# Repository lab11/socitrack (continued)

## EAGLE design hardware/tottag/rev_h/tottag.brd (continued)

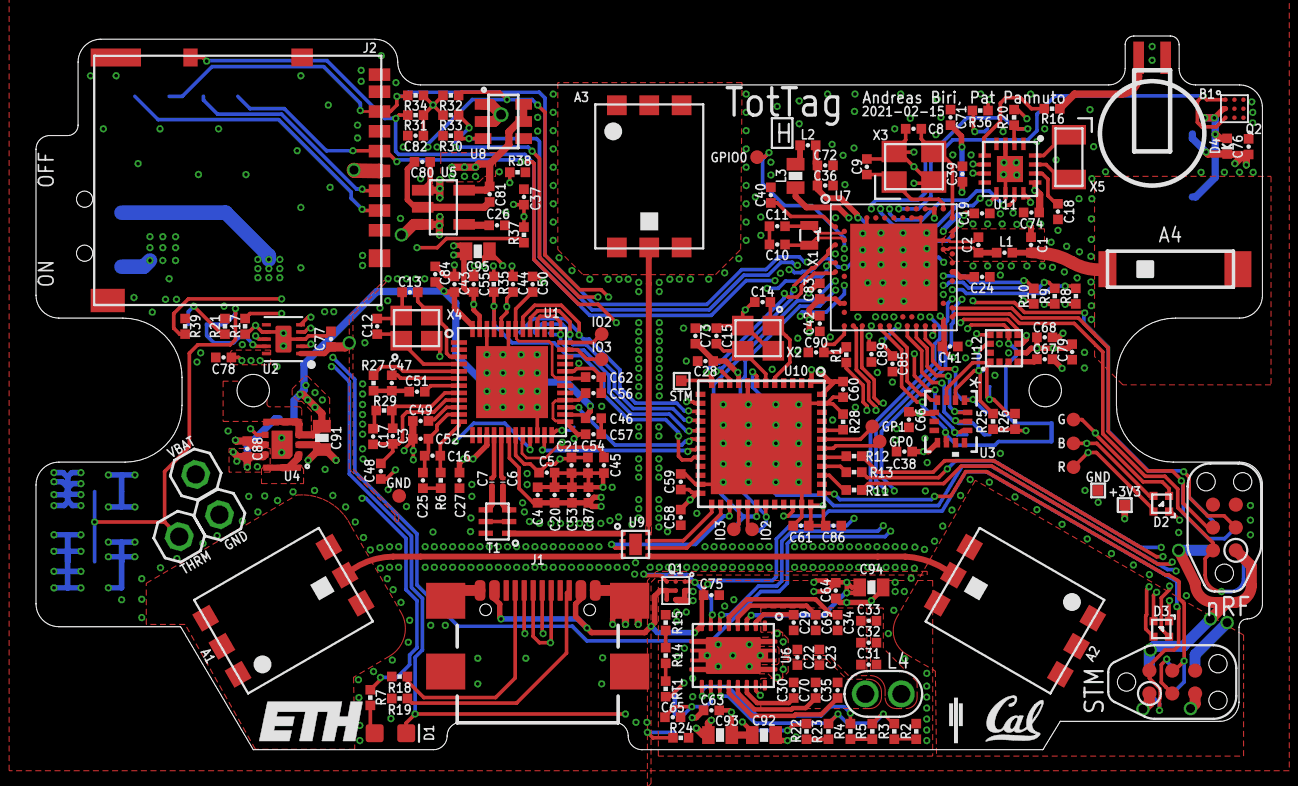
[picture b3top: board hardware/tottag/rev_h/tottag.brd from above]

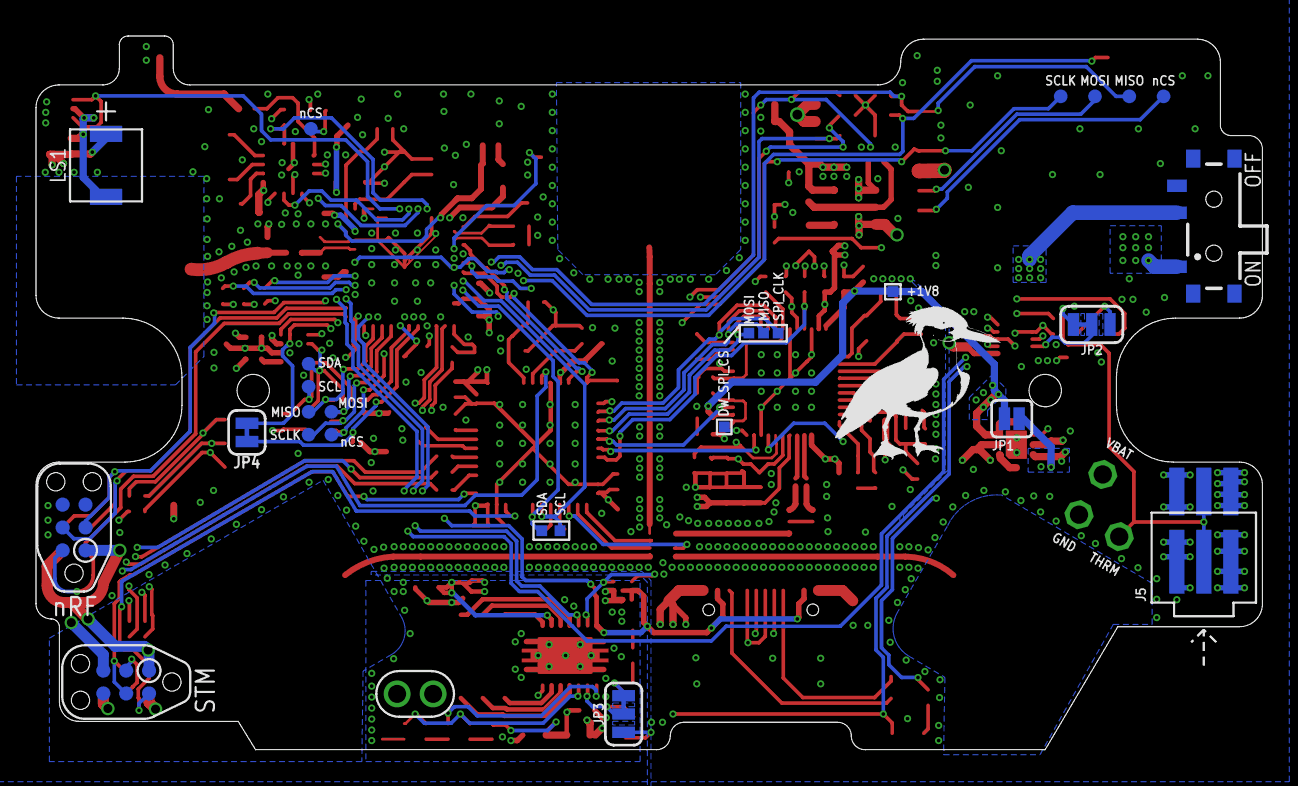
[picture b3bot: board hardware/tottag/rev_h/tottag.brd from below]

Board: 4 copper layers, 68.1 x 39.6 mm, 218 parts (26 on the bottom side), 150 nets.

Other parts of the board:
U$1: TOTTERNARY_300MIL
U$2: UCSD_TRIDENT_SOLID_100MIL
U$3: ETH_200MIL
U$4: UCB_CAL_100MIL

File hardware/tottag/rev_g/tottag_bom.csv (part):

# Bill of Materials,,,,,,,,,,,,
# Converted from {},,,,,,,,,,,,
# Generated by bom_to_text.py,,,,,,,,,,,,
#,,,,,,,,,,,,
,,,,,,,,,,,,
Qty,Parts,Value,Can Substitue,Do Not Populate (DNP),Device,Package,Description,DESCRIPTION,DIGIKEY,MANUFACTURER,MPN,MOUSER
3,"A1, A2, A3",TAIYO-YUDEN-AH086M,N,,TAIYO-YUDEN-AH086M,TAIYO-YUDEN-AH086M,UWB Antenna - 3.1-8GHz,,587-2204-1-ND,,AH086M555003-T,
1,A4,AMCA72-2R47G-S1F-T,N,,AMCA72-2R47G-S1F-T,AMCA72-2R470G-S1F-T,"WiFi/Bluetooth/ZigBee, ISM Atenna",RF ANT 2.4GHZ CHIP SOLDER SMD,535-14108-1-ND,,AMCA72-2R470G-S1F-T4,
1,C1,0.5pF,ASK,,CAPACITOR0402_CAP,0402_CAP,SMD Capacitor,,490-11250-1-ND,,GJM1555C1HR50WB01D,
1,C2,0.8pF,ASK,,CAPACITOR0402_CAP,0402_CAP,SMD Capacitor,,490-11253-1-ND,,GJM1555C1HR80WB01D,
1,C3,1.2pF,ASK,,CAPACITOR0402_CAP,0402_CAP,SMD Capacitor,,490-3085-1-ND,,GJM1555C1H1R2CB01D,
2,"C4, C5",10pF,Y,,CAPACITOR0402_CAP,0402_CAP,SMD Capacitor,,732-12054-1-ND,,885012005074,
2,"C6, C7",12pF,ASK,,CAPACITOR0201_CAP,0201_CAP,SMD Capacitor,,399-8604-2-ND,,CBR02C120F3GAC,
8,"C8, C9, C10, C11, C12, C13, C14, C15",12pF,ASK,,CAPACITOR0402_CAP,0402_CAP,SMD Capacitor,,399-8815-2-ND,,CBR04C120F5GAC,
1,C16,18pF,ASK,,CAPACITOR0402_CAP,0402_CAP,SMD Capacitor,,399-8828-1-ND,,CBR04C180F5GAC,
1,C17,27pF,ASK,,CAPACITOR0402_CAP,0402_CAP,SMD Capacitor,,490-16380-1-ND,,GJM1555C1H270FB01D,
1,C18,47pF,Y,,CAPACITOR0402_CAP,0402_CAP,SMD Capacitor,,490-5942-1-ND,,GRM1555C1H470JA01D ,
1,C19,100pF,Y,,CAPACITOR0402_CAP,0402_CAP,SMD Capacitor,,490-5922-1-ND,,GRM1555C1H101JA01D ,
2,"C20, C21",330pF,Y,,CAPACITOR0402_CAP,0402_CAP,SMD Capacitor,,311-3768-1-ND,,CC0402JRX7R9BB331,
2,"C22, C23",470pF,Y,,CAPACITOR0402_CAP,0402_CAP,SMD Capacitor,CAP CER 470PF 50V C0G/NP0 0402,490-6242-1-ND,Murata,GRM1555C1H471JA01J,
2,"C24, C25",820pF,ASK,,CAPACITOR0402_CAP,0402_CAP,SMD Capacitor,,399-11129-2-ND,,C0402C821J5GACTU,
5,"C26, C27, C28, C29, C30",10nF,Y,,CAPACITOR0402_CAP,0402_CAP,SMD Capacitor,,490-6351-2-ND,,GRM155R71H103KA88J,
5,"C31, C32, C33, C34, C35",22nF,ASK,,CAPACITOR0402_CAP,0402_CAP,SMD Capacitor,,311-3823-1-ND,,CC0402ZRY5V8BB223,
1,C36,47nF,Y,,CAPACITOR0402_CAP,0402_CAP,SMD Capacitor,,445-1264-1-ND,,C1005X7R1C473K050BC ,
29,"C37, C38, C39, C40, C41, C42, C43, C44, C45, C46, C47, C48, C49, C50, C51, C52, C53, C54, C55, C56, C57, C58, C59, C60, C61, C62, C63, C64, C65",0.1uF,Y,,CAPACITOR0402_CAP,0402_CAP,SMD Capacitor,,399-C0402C104K4RAC7411TR-ND,,C0402C104K4RAC7411,
2,"C66, C67",470nF,Y,,CAPACITOR0402_CAP,0402_CAP,SMD Capacitor,,490-12270-1-ND,,GRT155R61E474ME01D,
8,"C68, C69, C70, C71, C72, C73, C74, C75",1uF,Y,,CAPACITOR0402_CAP,0402_CAP,SMD Capacitor,,490-7195-1-ND ,,GRM155R70G105KA12D ,
11,"C76, C77, C78, C79, C80, C81, C82, C83, C84, C85, C86",4.7uF,Y,,CAPACITOR0402_CAP,0402_CAP,SMD Capacitor,CAP CER 4.7UF 6.3V X5R 0402,445-13820-2-ND,TDK,C1005X5R1A475K050BC,
5,"C87, C88, C89, C90, C91",10uF,Y,,CAPACITOR0603_CAP,0603_CAP,SMD Capacitor,,1253-CM105X5R106M25ATCT-ND,,CM105X5R106M25AT,
1,C92,47uF,Y,,CAPACITOR0603_CAP,0603_CAP,SMD Capacitor,,490-13247-1-ND,,GRM188R60J476ME15D,
1,D1,GREEN,Y,,LED0603,LED-0603,LED (Generic),,160-1446-1-ND,,LTST-C191KGKT,
2,"D2, D3",SML-LX0404SIUPGUSB,Y,,SML-LX0404SIUPGUSB,1MM_SQ_4PAD,1mm^2 RGB LED,,67-2125-1-ND,Lumex Opto,SML-LX0404SIUPGUSB,
1,D4,DIODE0402,Y,,DIODE0402,0402_DIODE,,,641-2087-1-ND,,CDSQR400B-HF,
1,J1,USB4110-GF-A,N,,USB4110-GF-A,GCT_USB4110-GF-A,CONN USB 2.0 TYPE-C R/A SMT," USB-C (USB TYPE-C) USB 2.0 Receptacle Connector 24 (16+8 Dummy) Position Surface Mount, Right Angle",2073-USB4110-GF-A-1-ND,,USB4110-GF-A,
1,J2,DM3AT-SF-PEJM5,N,,DM3AT-SF-PEJM5,DM3AT-SF-PEJM5,CONN MICRO SD R/A PUSH-PUSH SMD,CONN MICRO SD CARD PUSH-PUSH R/A,HR1964CT-ND,Hirose Electric Co Ltd,DM3AT-SF-PEJM5,
1,J5,MOLEX-PICO-SPOX-3SIDE,N,,MOLEX-PICO-SPOX-3SIDE,MOLEX-PICO-SPOX-3_SIDE,MOLEX,,WM7647CT-ND,,874380343,
1,L1,4.7nH,ASK,,INDUCTOR0402,0402_CAP,A very specific inductor,,490-15482-1-ND,,LQW15AN4N7G8ZD,
1,L2,15nH,ASK,,INDUCTOR0402,0402_CAP,A very specific inductor,,587-1521-1-ND,,HK100515NJ-T ,
1,L3,10uH,ASK,,INDUCTOR0603,0603_CAP,A very specific inductor,,490-4025-1-ND,,LQM18FN100M00D ,
1,LS1,PUI_SMT-0440-T-2-R,N,,PUI_SMT-0440-T-2-R,SMT-0440-T-2-R,,,668-SMT-0440-T-2-RTR-ND,,SMT-0440-T-2-R,
2,"Q1, Q2",CSD75207W15,N,,CSD75207W15,DSBGA,"low on resistance, gate charge dual p-channel nexfet",,296-40008-1-ND,TEXAS INSTRUMENTS,CSD75207W15,
1,R1,4.7,Y,,RESISTOR0402_RES,0402_RES,Resistor,,RMCF0402FT4R70CT-ND,,RMCF0402FT4R70,
2,"R2, R3",97.6,ASK,,RESISTOR0402_RES,0402_RES,Resistor,,RMCF0402FT97R6CT-ND,,RMCF0402FT97R6,
2,"R4, R5",162,ASK,,RESISTOR0402_RES,0402_RES,Resistor,,RMCF0402FT162RCT-ND,,RMCF0402FT162R,
1,R6,270,Y,,RESISTOR0402_RES,0402_RES,Resistor,,RMCF0402FT270RCT-ND,,RMCF0402FT270R,
9,"R7, R8, R9, R10, R11, R12, R13, R14, R15",1k,Y,,RESISTOR0402_RES,0402_RES,Resistor,,RMCF0402FT1K00CT-ND,,RMCF0402FT1K00,
1,R16,1.41k,Y,,RESISTOR0402_RES,0402_RES,Resistor,,RMCF0402FT1K40CT-ND,,RMCF0402FT1K40,
1,R17,2.2k,Y,,RESISTOR0402_RES,0402_RES,Resistor,,RMCF0402JT2K20CT-ND,,RMCF0402JT2K20,
2,"R18, R19",5.1k,Y,,RESISTOR0402_RES,0402_RES,Resistor,,RMCF0402FT5K10CT-ND,,RMCF0402FT5K10,
5,"R20, R21, R22, R23, R24",10k,Y,,RESISTOR0402_RES,0402_RES,Resistor,,RMCF0402FT10K0CT-ND,,RMCF0402FT10K0,
2,"R25, R26",11k,Y,,RESISTOR0402_RES,0402_RES,Resistor,,RMCF0402FT11K0CT-ND,,RMCF0402FT11K0,
1,R27,16k,Y,,RESISTOR0402_RES,0402_RES,Resistor,,RMCF0402FT16K0CT-ND,,RMCF0402FT16K0,
7,"R28, R29, R30, R31, R32, R33, R34",100k,Y,,RESISTOR0402_RES,0402_RES,Resistor,,RMCF0402JT100KCT-ND,,RMCF0402JT100K,
1,R35,3.3M,Y,,RESISTOR0402_RES,0402_RES,Resistor,,RMCF0402FT3M30CT-ND,,RMCF0402FT3M30,
1,R36,10M,Y,,RESISTOR0402_RES,0402_RES,Resistor,,RMCF0402FT10M0CT-ND,,RMCF0402FT10M0,
1,R37,DNP,,DNP,RESISTOR0402_RES,0402_RES,Resistor,,,,,
1,RT1,10k@25C,ASK,,THERMISTOR0402,0402_RES,Thermistor.,,490-18149-1-ND,,NCU15XH103F60RC,
1,S1,,N,,450404015514,450404015514,"WS-SLSU Mini Slide Switch, Same Side Connection Side Push 6.7x2.7 mm",,732-13665-1-ND,,450404015514,
1,T1,HHM1595A1,N,,HHM1595A1,EIA-0805,"Description: Symbol for HHM1595A1, a multilayer Balun from TDK.",XFMR BALUN RF 3.0-8.0GHZ UWB SMD,445-3387-1-ND,TDK Corporation,HHM1595A1,810-HHM1595A1
1,U1,DW1000,N,,DW1000,QFN-48-DW1000,"Description: The DecaWave DW1000 chip, used for UWB two-way ranging.",IC RF TXRX 802.15.4 48-QFN,1479-1001-1-ND,Decawave Limited,DW1000-I-TR13,
1,U2,BQ24040,N,,BQ24040,DSQ0010A,Simple Li Ion / Li Poly charger.,,296-37142-1-ND,,BQ24040,
1,U3,LIS2DW12,N,,LIS2DW12,LGA-12,ultra low power 3 axis accelerometer,,497-17718-6-ND,STMicroelectronics,LIS2DW12TR,511-LIS2DW12TR
1,U4,1.8V,N,,XCL206B,XCL20X,Non-Isolated PoL Module DC DC Converter 1 Output 1.8V 600mA 2V - 6V Input,,893-1406-2-ND,,XCL206B183CR-G,
1,U5,MAX8887EZK33+T,N,,MAX8887EZK33+T,SOT-23-5,IC REG LDO 3.3V 0.3A TSOT23-5,,MAX8887EZK33+TCT-ND,,,
1,U6,BQ51013B,N,,BQ51013B,RHL0020A,bq51013B,,296-38885-1-ND,,BQ51013B,
1,U7,NRF52840,N,,NRF52840,AQFN73,"ultra-low power 2.4 GHz wireless system on chip (SoC) integrating a multiprotocol 2.4 GHz transceiver, an ARM® Cortex®-M4F CPU.",,1490-1071-1-ND,NORIDIC SEMICONDUCTOR,NRF52840,
1,U8,SIP32510,N,,SIP32510,TSOT23-6,"Load switch, slew rate controlled. By Vishay",, SIP32510DT-T1-GE3CT-ND,Vishay,SIP32510DT-T1-GE3,
1,U9,SKY13317,N,,SKY13317,MLPQ-UT-8,"Description: Device for SKY13317-373LF, an RF switch from Skyworks Inc.",IC SWITCH RF SP3T 8-MLP,863-1056-1-ND,Skyworks Solutions Inc.,SKY13317-373LF,
1,U10,STM32F091CC,N,,STM32F091CC,UFQFPN-48,"Description: STM32F091CC from STMicroelectronics, an ARM-based 32-bit MCU with 256 kB Flash, 32kB of SRAM and a Cortex M0",IC MCU 32BIT 256KB FLASH 48QFPN,497-15813-ND,STMicroelectronics,STM32F091CCU6,511-STM32F091CCU6
1,U11,AB1815-T3,N,,AB1815-T3,QFN-16-3MM,Ultra-low current RTC. 55nA quiescent @ 3V. 1.5-3.6V input.,,535-11936-1-ND,Abracon,AB1815-T3,
1,X1,32.768kHz,N,,ABS05-32.768KHZ-9-T,ABS05,32.768kHz Crystal,,535-11897-1-ND,Abracon,ABS05-32.768KHZ-9-T,
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
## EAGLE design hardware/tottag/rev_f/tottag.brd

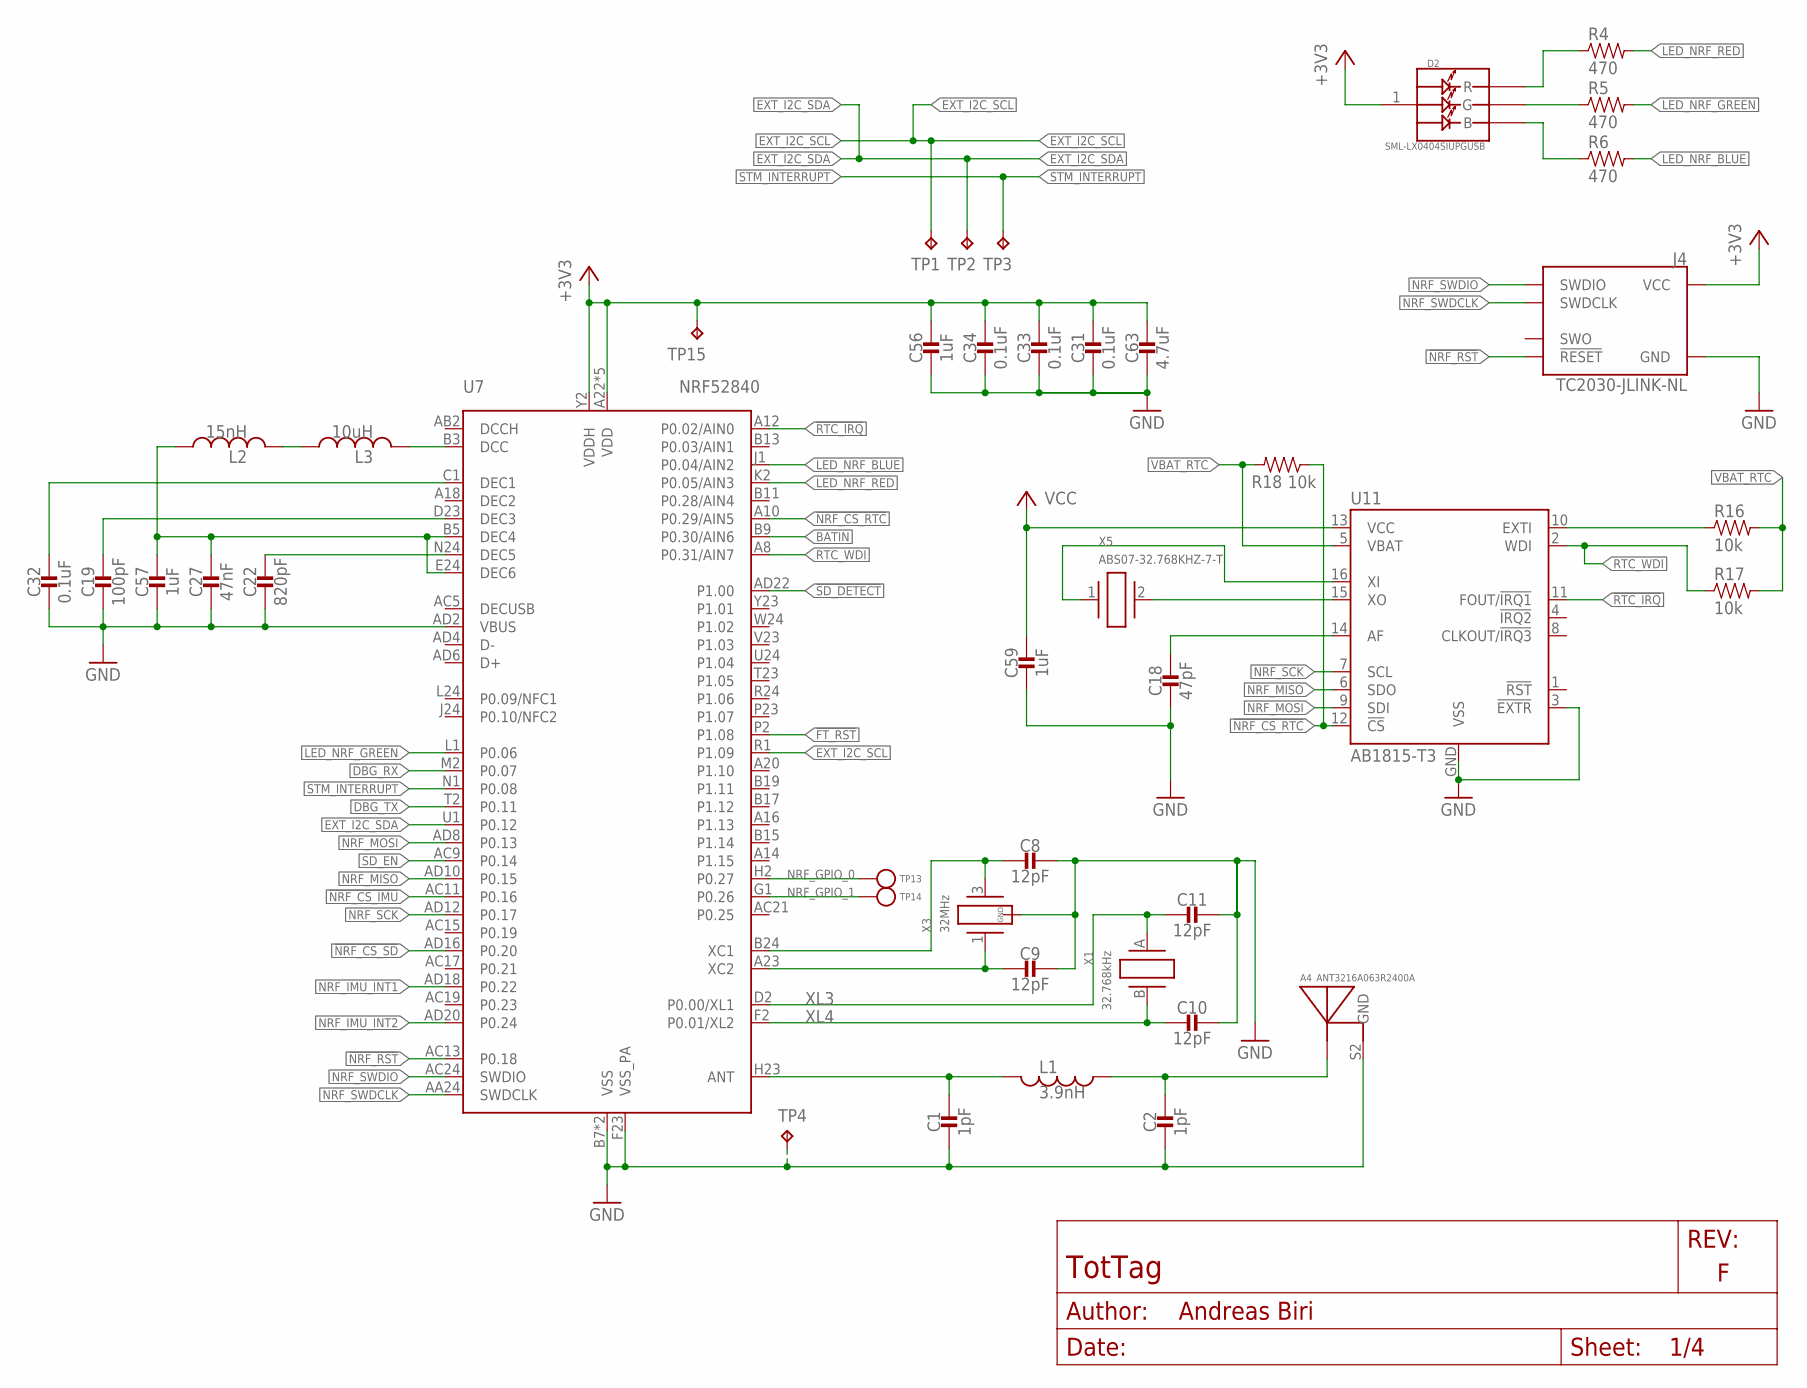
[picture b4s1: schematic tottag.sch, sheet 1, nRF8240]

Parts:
A4: ANT3216A063R2400A
C1, C2: 1pF; 0402_CAP; MPN GJM1555C1H1R0CB01D; DIGIKEY 490-3083-1-ND
C8, C9, C10, C11: 12pF; 0402_CAP; MPN GRM1555C1H120GA01D; DIGIKEY 490-6197-1-ND
C18: 47pF; 0402_CAP; MPN GRM1555C1H470JA01D; DIGIKEY 490-5942-1-ND
C19: 100pF; 0402_CAP; MPN GRM1555C1H101JA01D; DIGIKEY 490-5922-1-ND
C22: 820pF; 0402_CAP; MPN CL05C821JB5NFNC; DIGIKEY 1276-6989-1-ND
C27: 47nF; 0402_CAP; MPN C1005X7R1C473K050BC; DIGIKEY 445-1264-1-ND
C31, C32, C33: 0.1uF; 0402_CAP; MPN GRM155R71C104KA88J; DIGIKEY 490-6328-1-ND
C34: 0.1uF; 0402_CAP
C56: 1uF; 0402_CAP
C57, C59: 1uF; 0402_CAP; MPN GRM155R70G105KA12D; DIGIKEY 490-7195-1-ND
C63: 4.7uF; 0402_CAP
D2: SML-LX0404SIUPGUSB; 1MM_SQ_4PAD
J4: TC2030-JLINK-NL; TC2030-IDC-NL
L1: 3.9nH; 0402_CAP; MPN AISC-0402-3N9G-T; DIGIKEY AISC-0402-3N9G-TCT-ND
L2: 15nH; 0402_CAP; MPN HK100515NJ-T; DIGIKEY 587-1521-1-ND
L3: 10uH; 0603_CAP; MPN LQM18FN100M00D; DIGIKEY 490-4025-1-ND
R4, R5, R6: 470; 0402_RES
R16, R17, R18: 10k; 0402_RES; MPN RC0402JR-0710KL; DIGIKEY 311-10KJRCT-ND
TP1, TP2, TP3, TP4, TP15: TPTP06SQ; TP06SQ
TP13, TP14: TEST-POINT; PAD.03X.03
U7: NRF52840; AQFN73
U11: AB1815-T3; QFN-16-3MM
X1: 32.768kHz; ABS05
X3: 32MHz; TXC-7V
X5: ABS07-32.768KHZ-7-T; 2-SMD

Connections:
!FT_RST: U7.P2 (P1.08); also elsewhere on the board
!NRF_CS_IMU: U7.AC11 (P0.16); also elsewhere on the board
!NRF_CS_RTC: R18.1, U7.A10 (P0.29/AIN5), U11.12 (!CS)
!NRF_CS_SD: U7.AD16 (P0.20); also elsewhere on the board
!NRF_RST: J4.3 (!RESET), U7.AC13 (P0.18)
!RTC_IRQ: U7.A12 (P0.02/AIN0), U11.11 (FOUT/!IRQ1)
!SD_DETECT: U7.AD22 (P1.00); also elsewhere on the board
+3V3: C31.1, C33.1, C34.1, C56.1, C63.1, D2.1 (VDD), J4.1 (VCC), TP15.TP, U7.A22 (VDD), U7.AD14 (VDD), U7.AD23 (VDD), U7.B1 (VDD), U7.W1 (VDD), U7.Y2 (VDDH); also elsewhere on the board
BATIN: U7.B9 (P0.30/AIN6); also elsewhere on the board
DBG_RX: U7.M2 (P0.07); also elsewhere on the board
DBG_TX: U7.T2 (P0.11); also elsewhere on the board
EXT_I2C_SCL: TP1.TP, U7.R1 (P1.09); also elsewhere on the board
EXT_I2C_SDA: TP2.TP, U7.U1 (P0.12); also elsewhere on the board
GND: A4.S2 (GND), C1.2, C2.2, C8.1, C9.1, C10.1, C11.1, C18.2, C19.2, C22.2, C27.2, C31.2, C32.2, C33.2, C34.2, C56.2, C57.2, C59.2, C63.2, J4.5 (GND), TP4.TP, U7.AD2 (VBUS), U7.B7 (VSS), U7.F23 (VSS_PA), U7.GND (VSS), U11.3 (!EXTR), U11.GND (VSS), X3.2 (GND), X3.4 (GND); also elsewhere on the board
LED_NRF_BLUE: R6.2, U7.J1 (P0.04/AIN2)
LED_NRF_GREEN: R5.2, U7.L1 (P0.06)
LED_NRF_RED: R4.2, U7.K2 (P0.05/AIN3)
unnamed: C22.1, U7.N24 (DEC5)
unnamed: C32.1, U7.C1 (DEC1)
unnamed: C27.1, C57.1, L2.1, U7.B5 (DEC4), U7.E24 (DEC6)
unnamed: C19.1, U7.D23 (DEC3)
unnamed: C1.1, L1.2, U7.H23 (ANT)
unnamed: A4.S1 (ANTENNA), C2.1, L1.1
unnamed: C8.2, U7.B24 (XC1), X3.3 (2)
unnamed: C9.2, U7.A23 (XC2), X3.1
unnamed: L3.2, U7.B3 (DCC)
unnamed: C18.1, U11.14 (AF)
unnamed: L2.2, L3.1
unnamed: U11.16 (XI), X5.1
unnamed: U11.15 (XO), X5.2
unnamed: R16.1, U11.10 (EXTI)
unnamed: D2.2 (R), R4.1
unnamed: D2.4 (G), R5.1
unnamed: D2.3 (B), R6.1
NRF_GPIO_0: TP13.P$1, U7.H2 (P0.27)
NRF_GPIO_1: TP14.P$1, U7.G1 (P0.26)
NRF_IMU_INT1: U7.AD18 (P0.22); also elsewhere on the board
NRF_IMU_INT2: U7.AD20 (P0.24); also elsewhere on the board
NRF_MISO: U7.AD10 (P0.15), U11.6 (SDO); also elsewhere on the board
NRF_MOSI: U7.AD8 (P0.13), U11.9 (SDI); also elsewhere on the board
NRF_SCK: U7.AD12 (P0.17), U11.7 (SCL); also elsewhere on the board
NRF_SWDCLK: J4.4 (SWDCLK), U7.AA24 (SWDCLK)
NRF_SWDIO: J4.2 (SWDIO), U7.AC24 (SWDIO)
RTC_WDI: R17.1, U7.A8 (P0.31/AIN7), U11.2 (WDI)
SD_EN: U7.AC9 (P0.14); also elsewhere on the board
STM_INTERRUPT: TP3.TP, U7.N1 (P0.08); also elsewhere on the board
VBAT_RTC: R16.2, R17.2, R18.2, U11.5 (VBAT); also elsewhere on the board
VCC: C59.1, U11.13 (VCC)
XL3: C11.2, U7.D2 (P0.00/XL1), X1.A (1)
XL4: C10.2, U7.F2 (P0.01/XL2), X1.B (2)

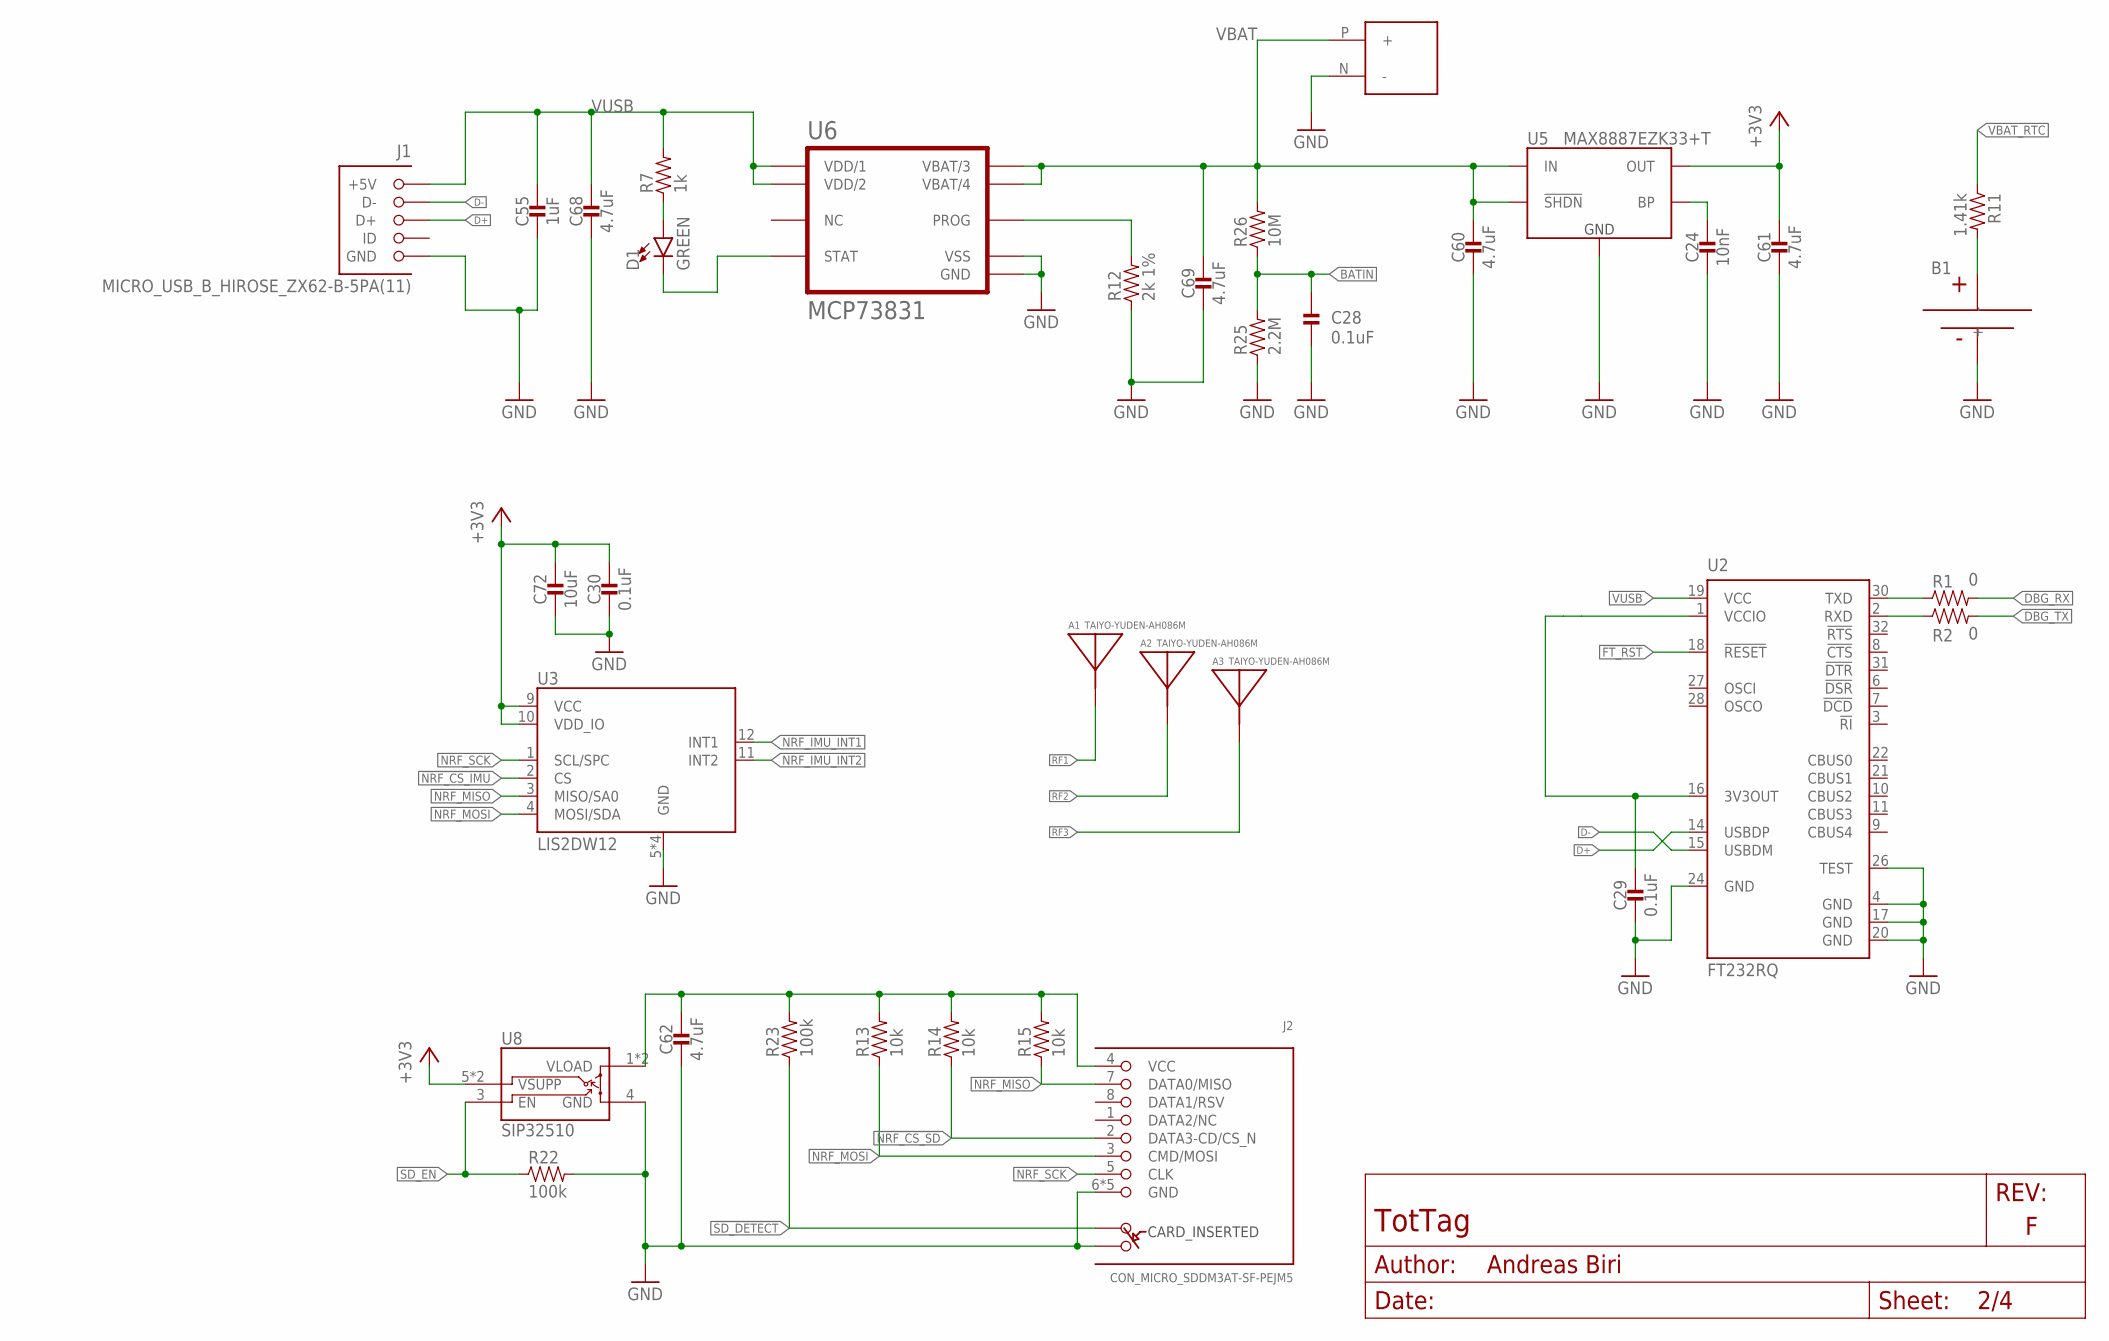
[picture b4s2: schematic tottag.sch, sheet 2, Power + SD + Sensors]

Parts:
A1, A2, A3: TAIYO-YUDEN-AH086M
B1: MS518SE; MS518SE-FL35E
C24: 10nF; 0402_CAP
C28: 0.1uF; 0402_CAP
C29, C30: 0.1uF; 0402_CAP; MPN GRM155R71C104KA88J; DIGIKEY 490-6328-1-ND
C55: 1uF; 0402_CAP
C60, C61, C68, C69: 4.7uF; 0402_CAP
C62: 4.7uF; 0402_CAP; MPN C1005X5R0J475K050BC; DIGIKEY 445-5947-1-ND
C72: 10uF; 0603_CAP; MPN GRM188R60J106ME47D; DIGIKEY 490-3896-1-ND
D1: GREEN; LED-0603
J1: MICRO_USB_B_HIROSE_ZX62-B-5PA(11); USB_MICRO_B-HIROSE-ZX62-B-5PA(11)
J2: CON_MICRO_SDDM3AT-SF-PEJM5; DM3AT-SF-PEJM5
J3: BAT_HOLE; BATTERY_HOLE
R1, R2: 0; 0402_RES
R7: 1k; 0402_RES
R11: 1.41k; 0402_RES; MPN RC0402JR-0710KL; DIGIKEY 311-10KJRCT-ND
R12: 2k 1%; 0402_RES
R13, R14, R15: 10k; 0402_RES
R22, R23: 100k; 0402_RES
R25: 2.2M; 0402_RES
R26: 10M; 0402_RES
U2: FT232RQ; QFN32
U3: LIS2DW12; LGA-12
U5: MAX8887EZK33+T; SOT-23-5
U6: MCP73831; DFN-8-MCP
U8: SIP32510; TSOT23-6

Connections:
!CHRG: D1.A, R7.1
!FT_RST: U2.18 (!RESET); also elsewhere on the board
!NRF_CS_IMU: U3.2 (CS); also elsewhere on the board
!NRF_CS_SD: J2.2 (DATA3-CD/CS_N), R14.1; also elsewhere on the board
!SD_DETECT: J2.A, R23.1; also elsewhere on the board
+3V3: C30.1, C61.1, C72.1, U3.9 (VCC), U3.10 (VDD_IO), U5.5 (OUT), U8.5 (VSUPP), U8.6 (VSUPP); also elsewhere on the board
BATIN: C28.2, R25.2, R26.1; also elsewhere on the board
D+: J1.3 (D+), U2.14 (USBDP)
D-: J1.2 (D-), U2.15 (USBDM)
DBG_RX: R1.2; also elsewhere on the board
DBG_TX: R2.2; also elsewhere on the board
GND: B1.-, C24.2, C28.1, C29.2, C30.2, C55.2, C60.2, C61.2, C62.2, C68.2, C69.2, C72.2, J1.5 (GND), J2.6 (GND), J2.B, J2.MOUNT0 (GND), J2.MOUNT1 (GND), J2.MOUNT2 (GND), J2.MOUNT3 (GND), J3.N (-), R12.1, R22.2, R25.1, U2.4 (GND), U2.17 (GND), U2.20 (GND), U2.24 (GND), U2.26 (TEST), U3.5 (GND), U3.6 (GND), U3.7 (GND), U3.8 (GND), U5.2 (GND), U6.6 (VSS), U6.GND, U8.4 (GND); also elsewhere on the board
unnamed: C29.1, U2.1 (VCCIO), U2.16 (3V3OUT)
unnamed: D1.C, U6.5 (STAT)
unnamed: C24.1, U5.4 (BP)
unnamed: R12.2, U6.8 (PROG)
unnamed: R1.1, U2.30 (TXD)
unnamed: R2.1, U2.2 (RXD)
unnamed: B1.+, R11.2
unnamed: C62.1, J2.4 (VCC), R13.2, R14.2, R15.2, R23.2, U8.1 (VLOAD), U8.2 (VLOAD)
NRF_IMU_INT1: U3.12 (INT1); also elsewhere on the board
NRF_IMU_INT2: U3.11 (INT2); also elsewhere on the board
NRF_MISO: J2.7 (DATA0/MISO), R15.1, U3.3 (MISO/SA0); also elsewhere on the board
NRF_MOSI: J2.3 (CMD/MOSI), R13.1, U3.4 (MOSI/SDA); also elsewhere on the board
NRF_SCK: J2.5 (CLK), U3.1 (SCL/SPC); also elsewhere on the board
RF1: A1.A; also elsewhere on the board
RF2: A2.A; also elsewhere on the board
RF3: A3.A; also elsewhere on the board
SD_EN: R22.1, U8.3 (EN); also elsewhere on the board
VBAT: C60.1, C69.1, J3.P (+), R26.2, U5.1 (IN), U5.3 (!SHDN), U6.3 (VBAT/3), U6.4 (VBAT/4)
VBAT_RTC: R11.1; also elsewhere on the board
VUSB: C55.1, C68.1, J1.1 (+5V), R7.2, U2.19 (VCC), U6.1 (VDD/1), U6.2 (VDD/2)

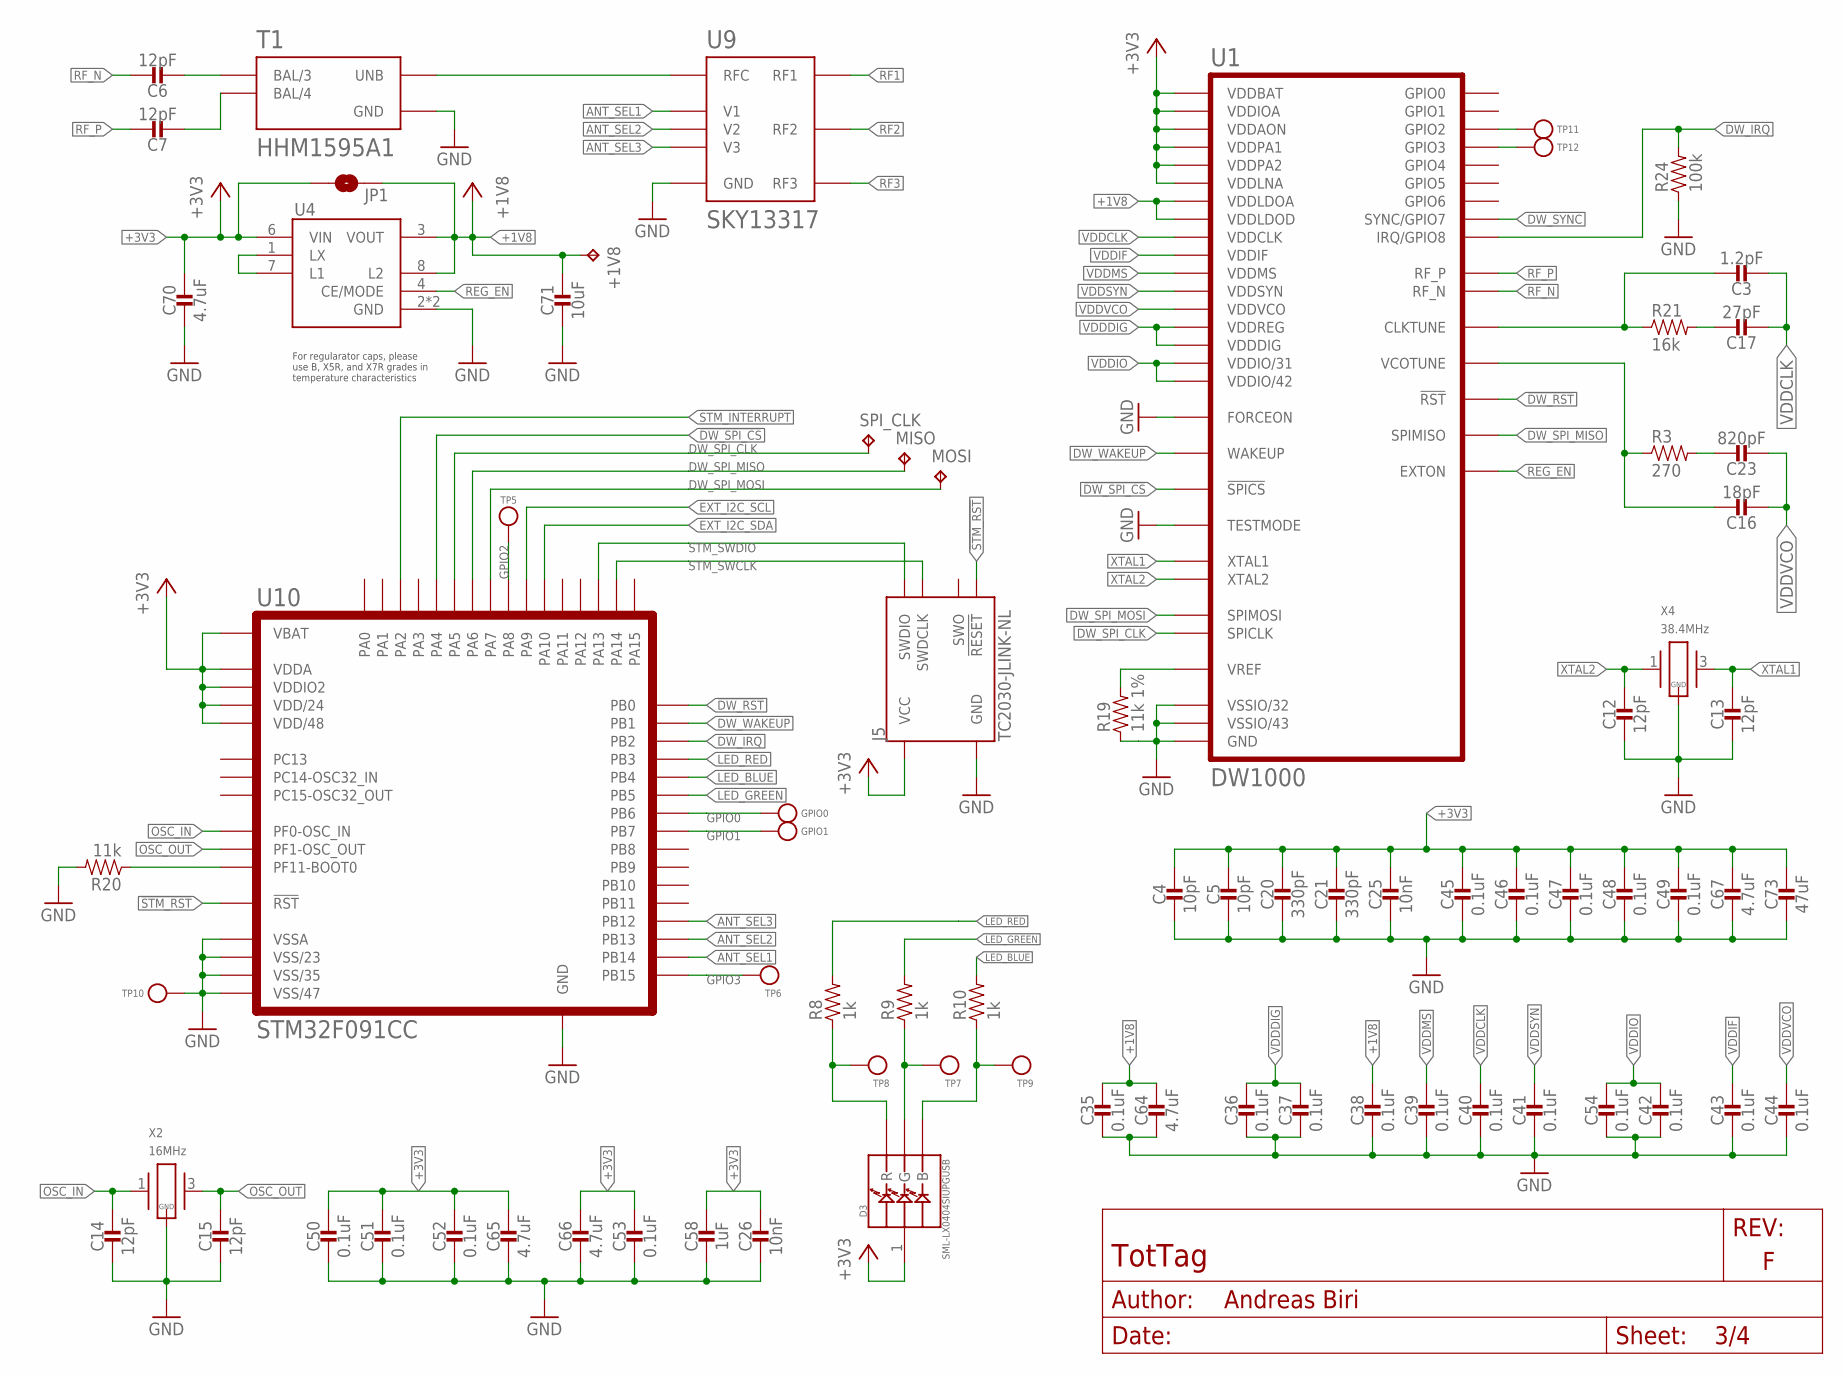
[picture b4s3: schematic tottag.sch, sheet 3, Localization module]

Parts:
+1V8: TPTP06SQ; TP06SQ
C3: 1.2pF; 0402_CAP
C4, C5: 10pF; 0402_CAP
C6, C7: 12pF; 0201_CAP
C12, C13, C14, C15: 12pF; 0402_CAP
C16: 18pF; 0402_CAP
C17: 27pF; 0402_CAP
C20, C21: 330pF; 0402_CAP
C23: 820pF; 0402_CAP
C25, C26: 10nF; 0402_CAP
C35, C36, C37, C38, C39, C40, C41, C42, C43, C44, C45, C46, C47, C48, C49, C50, C51, C52, C53, C54: 0.1uF; 0402_CAP
C58: 1uF; 0402_CAP
C64, C65, C66, C67, C70: 4.7uF; 0402_CAP
C71: 10uF; 0402_CAP
C73: 47uF; 0603_CAP
D3: SML-LX0404SIUPGUSB; 1MM_SQ_4PAD
GPIO0, GPIO1: TEST-POINT; PAD.03X.03
J5: TC2030-JLINK-NL; TC2030-IDC-NL
JP1: JUMPER-SMT_2_NO_NO-SILK; SMT-JUMPER_2_NO_NO-SILK
MISO: TPTP06SQ; TP06SQ
MOSI: TPTP06SQ; TP06SQ
R3: 270; 0402_RES
R8, R9, R10: 1k; 0402_RES
R19: 11k 1%; 0402_RES
R20: 11k; 0402_RES
R21: 16k; 0402_RES
R24: 100k; 0402_RES
SPI_CLK: TPTP06SQ; TP06SQ
T1: HHM1595A1; EIA-0805
TP5, TP6, TP7, TP8, TP9, TP10, TP11, TP12: TEST-POINT; PAD.03X.03
U1: DW1000; QFN-48-DW1000
U4: XCL206B; XCL20X
U9: SKY13317; MLPQ-UT-8
U10: STM32F091CC; UFQFPN-48
X2: 16MHz; FA-20H; DIGIKEY SER3913CT-ND
X4: 38.4MHz; FA-20H; DIGIKEY SER3631CT-ND

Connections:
!DW_RST: U1.27 (!RST), U10.18 (PB0)
!DW_SPI_CS: U1.24 (!SPICS), U10.14 (PA4)
!STM_RST: J5.3 (!RESET), U10.7 (!RST)
+1V8: +1V8.TP, C35.1, C38.1, C64.1, C71.1, JP1.2, U1.26 (VDDLDOD), U1.48 (VDDLDOA), U4.3 (VOUT), U4.8 (L2)
+3V3: C4.1, C5.1, C20.1, C21.1, C25.1, C26.1, C45.1, C46.1, C47.1, C48.1, C49.1, C50.1, C51.1, C52.1, C53.1, C58.1, C65.1, C66.1, C67.1, C70.1, C73.1, D3.1 (VDD), J5.1 (VCC), JP1.1, U1.15 (VDDLNA), U1.18 (VDDPA1), U1.19 (VDDPA2), U1.25 (VDDAON), U1.28 (VDDIOA), U1.47 (VDDBAT), U4.6 (VIN), U10.1 (VBAT), U10.9 (VDDA), U10.24 (VDD/24), U10.36 (VDDIO2), U10.48 (VDD/48); also elsewhere on the board
ANT_SEL1: U9.3 (V1), U10.27 (PB14)
ANT_SEL2: U9.6 (V2), U10.26 (PB13)
ANT_SEL3: U9.7 (V3), U10.25 (PB12)
DW_IRQ: R24.2, U1.45 (IRQ/GPIO8), U10.20 (PB2)
DW_SPI_CLK: SPI_CLK.TP, U1.41 (SPICLK), U10.15 (PA5)
DW_SPI_MISO: MISO.TP, U1.40 (SPIMISO), U10.16 (PA6)
DW_SPI_MOSI: MOSI.TP, U1.39 (SPIMOSI), U10.17 (PA7)
DW_SYNC: U1.29 (SYNC/GPIO7)
DW_WAKEUP: U1.23 (WAKEUP), U10.19 (PB1)
EXT_I2C_SCL: U10.30 (PA9); also elsewhere on the board
EXT_I2C_SDA: U10.31 (PA10); also elsewhere on the board
GND: C4.2, C5.2, C12.2, C13.2, C14.2, C15.2, C20.2, C21.2, C25.2, C26.2, C35.2, C36.2, C37.2, C38.2, C39.2, C40.2, C41.2, C42.2, C43.2, C44.2, C45.2, C46.2, C47.2, C48.2, C49.2, C50.2, C51.2, C52.2, C53.2, C54.2, C58.2, C64.2, C65.2, C66.2, C67.2, C70.2, C71.2, C73.2, J5.5 (GND), R19.1, R20.2, R24.1, T1.2 (GND), T1.5 (GND), TP10.P$1, U1.22 (FORCEON), U1.32 (VSSIO/32), U1.43 (VSSIO/43), U1.46 (TESTMODE), U1.GND, U4.2 (GND), U4.5 (GND), U9.GND, U10.8 (VSSA), U10.23 (VSS/23), U10.35 (VSS/35), U10.47 (VSS/47), U10.GND, X2.2 (GND), X2.4 (GND), X4.2 (GND), X4.4 (GND); also elsewhere on the board
GPIO0: GPIO0.P$1, U10.42 (PB6)
GPIO1: GPIO1.P$1, U10.43 (PB7)
GPIO2: TP5.P$1, U10.29 (PA8)
GPIO3: TP6.P$1, U10.28 (PB15)
LED_BLUE: R10.2, U10.40 (PB4)
LED_GREEN: R9.2, U10.41 (PB5)
LED_RED: R8.2, U10.39 (PB3)
unnamed: T1.1 (UNB), U9.1 (RFC)
unnamed: C6.P$2 (2), T1.3 (BAL/3)
unnamed: C7.P$2 (2), T1.4 (BAL/4)
unnamed: C23.1, R3.2
unnamed: C17.1, R21.2
unnamed: C16.1, R3.1, U1.12 (VCOTUNE)
unnamed: C3.1, R21.1, U1.8 (CLKTUNE)
unnamed: R19.2, U1.5 (VREF)
unnamed: R20.1, U10.44 (PF11-BOOT0)
unnamed: D3.4 (G), R9.1, TP7.P$1
unnamed: D3.3 (B), R10.1, TP9.P$1
unnamed: D3.2 (R), R8.1, TP8.P$1
unnamed: TP11.P$1, U1.36 (GPIO2)
unnamed: TP12.P$1, U1.35 (GPIO3)
unnamed: U4.1 (LX), U4.7 (L1)
OSC_IN: C14.1, U10.5 (PF0-OSC_IN), X2.1
OSC_OUT: C15.1, U10.6 (PF1-OSC_OUT), X2.3 (2)
REG_EN: U1.21 (EXTON), U4.4 (CE/MODE)
RF1: U9.4 (RF1); also elsewhere on the board
RF2: U9.5 (RF2); also elsewhere on the board
RF3: U9.8 (RF3); also elsewhere on the board
RF_N: C6.P$1 (1), U1.17 (RF_N)
RF_P: C7.P$1 (1), U1.16 (RF_P)
STM_INTERRUPT: U10.12 (PA2); also elsewhere on the board
STM_SWCLK: J5.4 (SWDCLK), U10.37 (PA14)
STM_SWDIO: J5.2 (SWDIO), U10.34 (PA13)
VDDCLK: C3.2, C17.2, C40.1, U1.9 (VDDCLK)
VDDDIG: C36.1, C37.1, U1.20 (VDDREG), U1.44 (VDDDIG)
VDDIF: C43.1, U1.7 (VDDIF)
VDDIO: C42.1, C54.1, U1.31 (VDDIO/31), U1.42 (VDDIO/42)
VDDMS: C39.1, U1.6 (VDDMS)
VDDSYN: C41.1, U1.10 (VDDSYN)
VDDVCO: C16.2, C23.2, C44.1, U1.11 (VDDVCO)
XTAL1: C13.1, U1.3 (XTAL1), X4.3 (2)
XTAL2: C12.1, U1.4 (XTAL2), X4.1

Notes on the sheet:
For regularator caps, please use B, X5R, and X7R grades in temperature characteristics
